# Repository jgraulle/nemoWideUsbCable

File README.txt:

Generate file for jlcpcb production:
- Run DRC check
- Generating Gerbers
   - File -> Fabrication Outputs -> Gerbers (.gbr)
   - Select the folder "buid"
   - Layer selection, List of layers that should be selected:
      - F.Cu
      - B.Cu
      - F.Paste
      - B.Paste
      - F.Silkscreen
      - B.Silkscreen
      - F.Mask
      - B.Mask
      - Edge.Cuts - (contain the board outline/cutouts.)
   - Jump to General Options and check these:
      - Select Plot reference designators, otherwise designators will not appear on silkscreen layers
      - Select Plot footprint text
      - Select Check zone fills before plotting
      - Select Tent vias
      - Select Use Protel filename extensions, this is recommended as JLCPCB prefers Protel filename extensions
      - Select Subtract soldermask from silkscreen, this ensures no silkscreen on pads
   - Click the Plot button at the bottom of the window
- Generate Drill files
   - From previous window press the "Generate Drill files..." button
   - Check Use alternate drill mode for "Oval Holes Drill Mode"
   - Check Absolute for "Drill Origin"
   - Check Millimeters for "Drill Units"
   - Check Decimal format for "Zeros Format"
   - Click the Generate Drill File button, the drill files will be generated and stored in the output folder
- Generate Drill Map file
   - From previous window press the "Generate Map File" button and everything is going to be done automatically.
- Generate Bill of Materials
   - From Schematic Layout Editor. From the menu bar, click Tool -> Generate Bill of Materials
   - In edit tab, Only check in this order:
      - "Value" with label "Comment"
      - "Reference" with label "Designator"
      - "Package" with label "Footprint"
      - "LCSC" with label "LCSC part number"
   - In export tab:
      - Set output file "build/maresUsbCable.csv"
      - Clic on export
- Generate Pick and Place files
   - From the PCB editor, click on File -> Fabrication output -> Footprint position (.pos) file and export the file with the following settings:
      - CSV
      - mm
      - One file per side
      - Use drilling/placement origin
   - Run the scrip "jlcGenerate.sh"

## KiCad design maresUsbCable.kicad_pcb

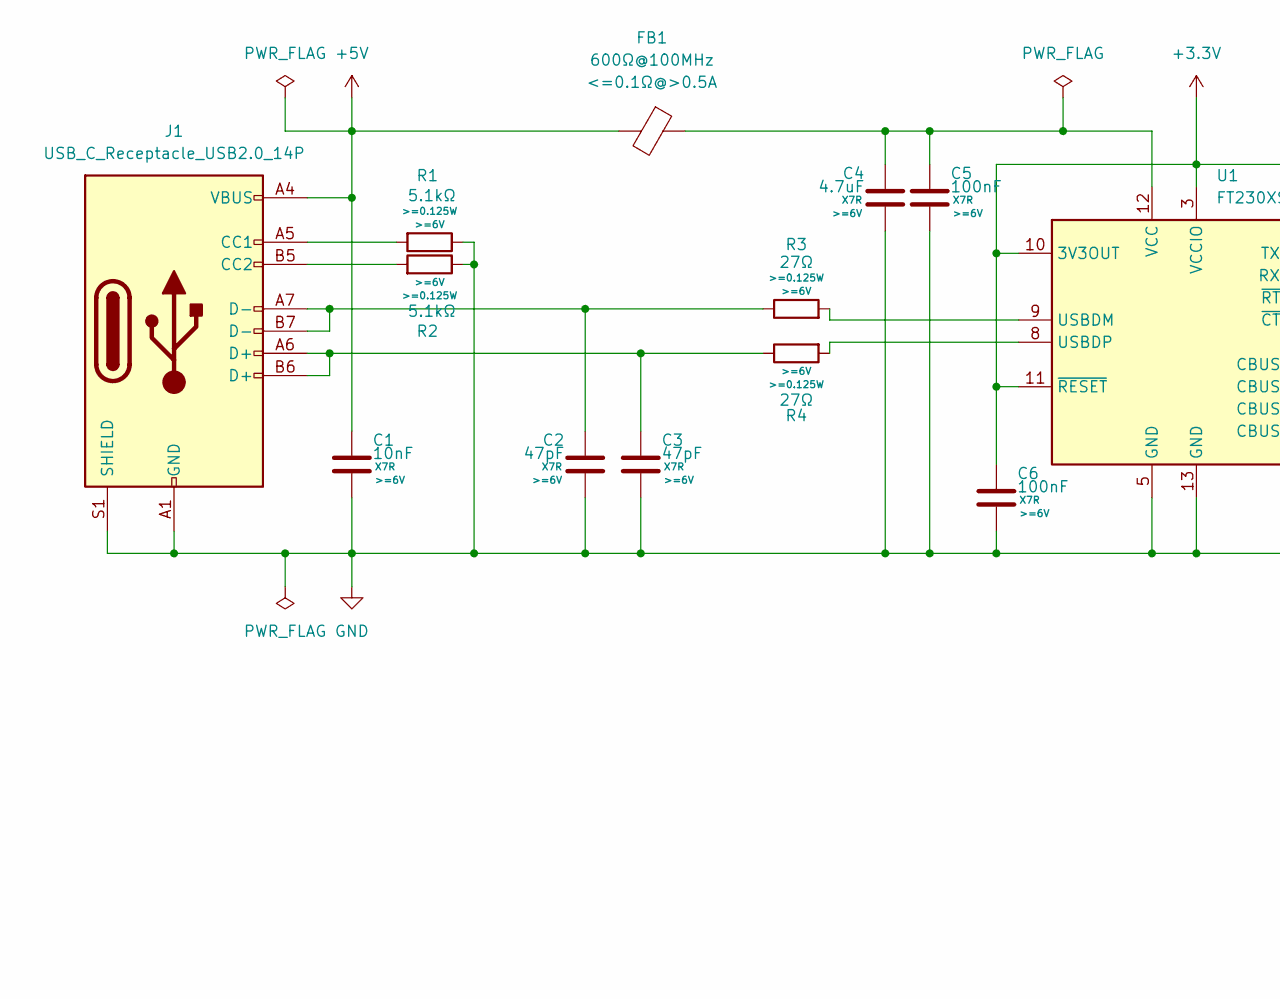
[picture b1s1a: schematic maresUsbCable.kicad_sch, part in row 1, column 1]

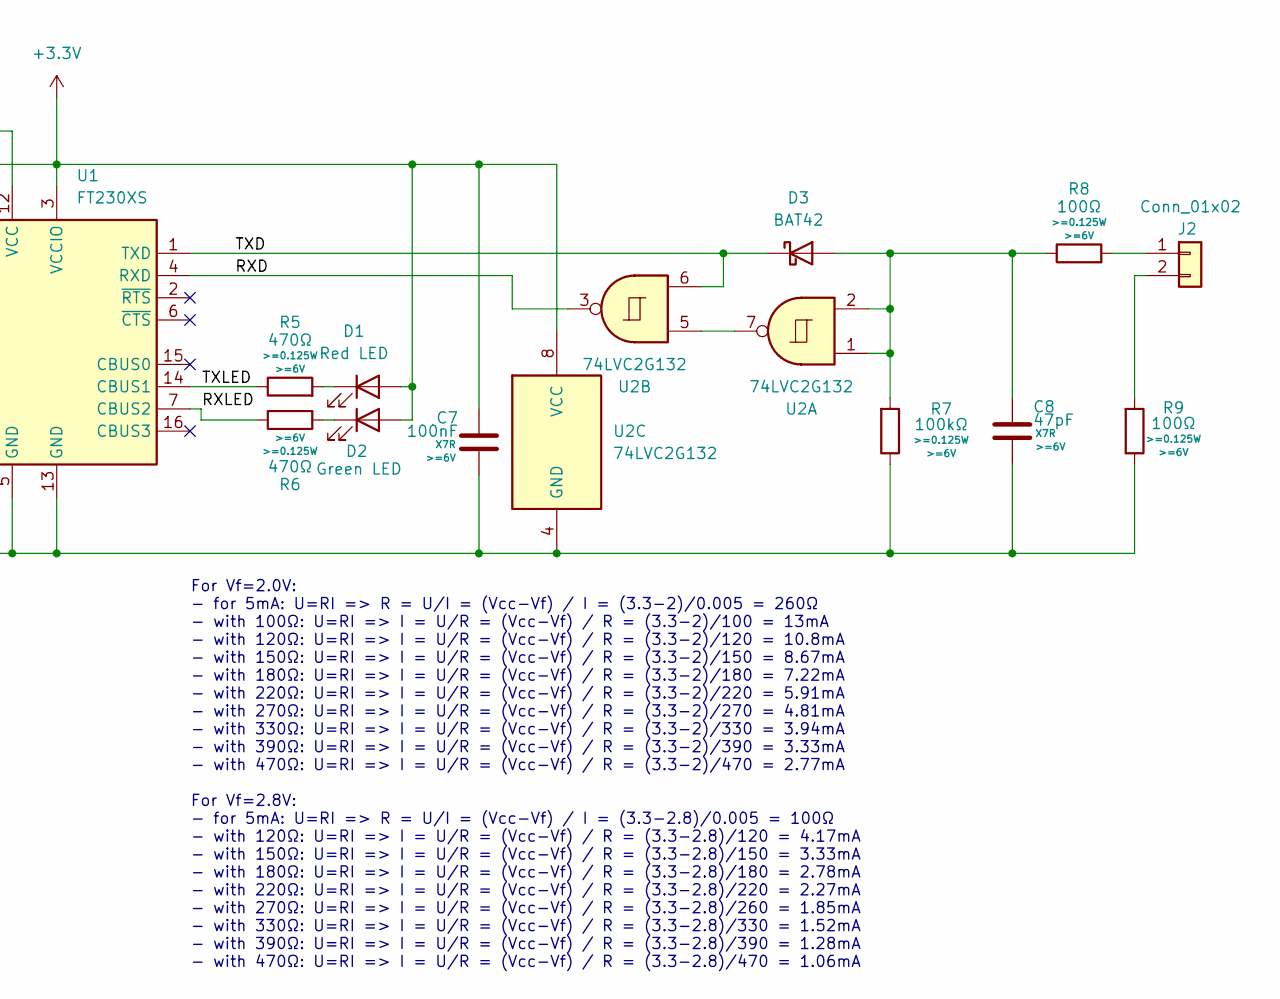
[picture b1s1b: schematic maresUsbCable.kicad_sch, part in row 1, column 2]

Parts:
C1: 10nF; C_0805_2012Metric; Voltage >=6V; Tolerance <=10%; LCSC-Manufacturer Samsung
C2, C3, C8: 47pF; C_0805_2012Metric; Voltage >=6V; Tolerance <=10%; LCSC-Manufacturer Samsung
C4: 4.7uF; C_0805_2012Metric; Voltage >=6V; Tolerance <=10%; LCSC-Manufacturer Samsung
C5, C6, C7: 100nF; C_0805_2012Metric; Voltage >=6V; Tolerance <=10%; LCSC-Manufacturer Samsung
D1: Red LED; LED_0805_2012Metric; LCSC-Manufacturer Foshan NationStar Optoelectronics
D2: Green LED; LED_0805_2012Metric; LCSC-Manufacturer Hubei KENTO Elec
D3: BAT42; D_SOD-123; LCSC-Manufacturer Vishay Intertech
FB1: 600Ω@100MHz; R_0805_2012Metric; Tolerance <=25%; LCSC-Manufacturer Sunlord
J1: USB_C_Receptacle_USB2.0_14P; USB_C_Receptacle_G-Switch_GT-USB-7010ASV; LCSC-Manufacturer G-Switch
J2: Conn_01x02; SolderWire_1x02_P12.7mm_D1.5mm
R1, R2: 5.1kΩ; R_0805_2012Metric; Voltage >=6V; Tolerance <=1%; LCSC-Manufacturer UNI-ROYAL(Uniroyal Elec)
R3, R4: 27Ω; R_0805_2012Metric; Voltage >=6V; Tolerance <=1%; LCSC-Manufacturer UNI-ROYAL(Uniroyal Elec)
R5, R6: 470Ω; R_0805_2012Metric; Voltage >=6V; Tolerance <=1%
R7: 100kΩ; R_0805_2012Metric; Voltage >=6V; Tolerance <=1%
R8, R9: 100Ω; R_0805_2012Metric; Voltage >=6V; Tolerance <=1%; LCSC-Manufacturer UNI-ROYAL(Uniroyal Elec)
U1: FT230XS; SSOP-16_3.9x4.9mm_P0.635mm; LCSC-Manufacturer FTDI
U2: 74LVC2G132; SSOP-8_3x3mm_P0.65mm; LCSC-Manufacturer Texas Instruments

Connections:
+3.3V: C6.2, C7.2, D1.2 (A), D2.2 (A), U1.3 (VCCIO), U1.10 (3V3OUT), U1.11 (~RESET), U2.8 (VCC)
+5V: C1.2, FB1.2, J1.A4 (VBUS), J1.A9 (VBUS), J1.B4 (VBUS), J1.B9 (VBUS)
/RXD: U1.4 (RXD), U2.3
/RXLED: R6.1, U1.7 (CBUS2)
/TXD: D3.1 (K), U1.1 (TXD), U2.6
/TXLED: R5.1, U1.14 (CBUS1)
GND: C1.1, C2.1, C3.1, C4.1, C5.1, C6.1, C7.1, C8.1, J1.A1 (GND), J1.A12 (GND), J1.B1 (GND), J1.B12 (GND), J1.S1 (SHIELD), R1.1, R2.1, R7.1, R9.1, U1.5 (GND), U1.13 (GND), U2.4 (GND)
unnamed: C2.2, J1.A7 (D-), J1.B7 (D-), R3.1
unnamed: C3.2, J1.A6 (D+), J1.B6 (D+), R4.1
unnamed: D1.1 (K), R5.2
unnamed: D2.1 (K), R6.2
unnamed: C8.2, D3.2 (A), R7.2, R8.1, U2.1, U2.2
unnamed: J1.A5 (CC1), R1.2
unnamed: J1.B5 (CC2), R2.2
unnamed: J2.1, R8.2
unnamed: J2.2, R9.2
unnamed: R3.2, U1.9 (USBDM)
unnamed: R4.2, U1.8 (USBDP)
unnamed: C4.2, C5.2, FB1.1, U1.12 (VCC)
unnamed: U2.5, U2.7

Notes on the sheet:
For Vf=2.0V: - for 5mA: U=RI => R = U/I = (Vcc-Vf) / I = (3.3-2)/0.005 = 260Ω - with 100Ω: U=RI => I = U/R = (Vcc-Vf) / R = (3.3-2)/100 = 13mA - with 120Ω: U=RI => I = U/R = (Vcc-Vf) / R = (3.3-2)/120 = 10.8mA - with 150Ω: U=RI => I = U/R = (Vcc-Vf) / R = (3.3-2)/150 = 8.67mA - with 180Ω: U=RI => I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

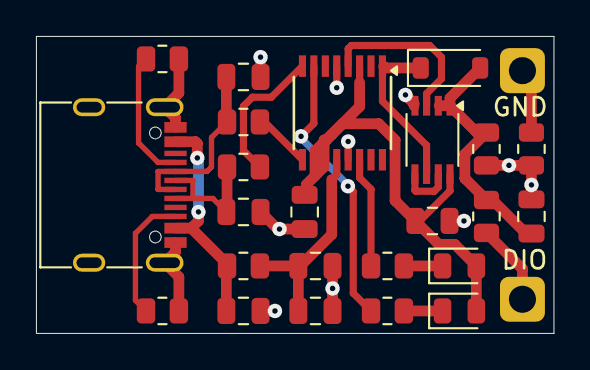
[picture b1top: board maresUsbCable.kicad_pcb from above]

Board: 2 copper layers, 28.8 x 16.5 mm, 25 parts (0 on the bottom side), 20 nets.

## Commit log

2024-12-29 Add missing 3d component
2024-12-30 Improve some routing
2025-01-11 Fix pull-down and LED resistance value
2025-04-02 Add plastic case
